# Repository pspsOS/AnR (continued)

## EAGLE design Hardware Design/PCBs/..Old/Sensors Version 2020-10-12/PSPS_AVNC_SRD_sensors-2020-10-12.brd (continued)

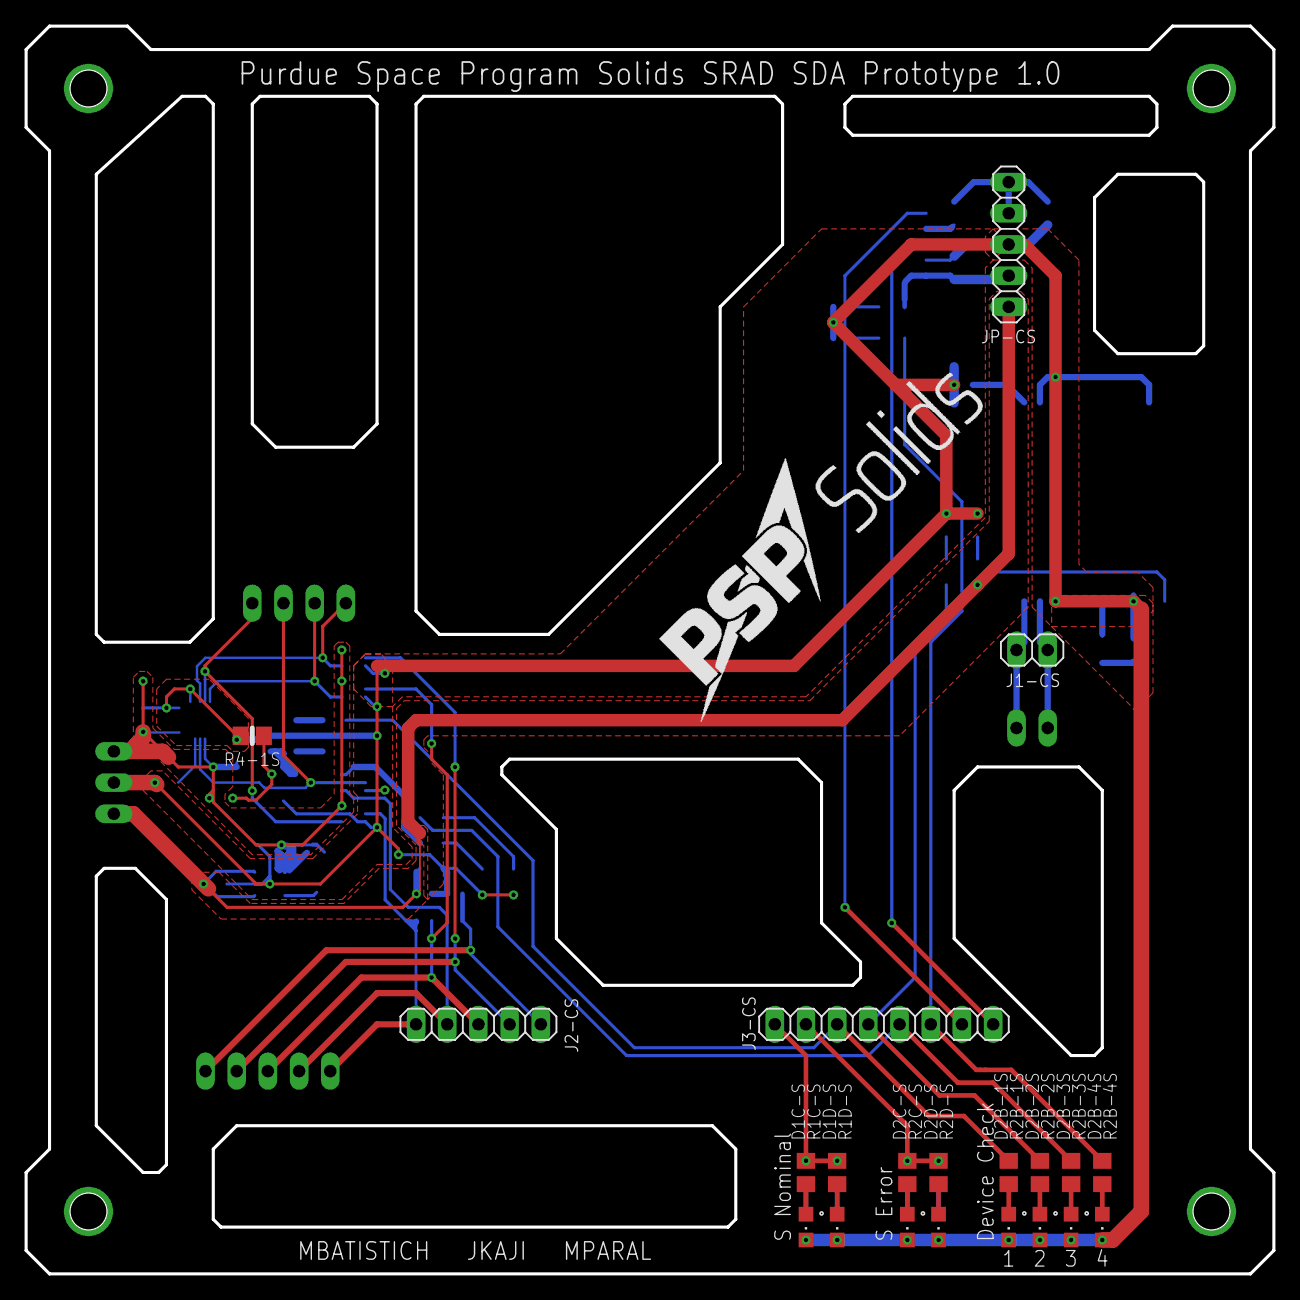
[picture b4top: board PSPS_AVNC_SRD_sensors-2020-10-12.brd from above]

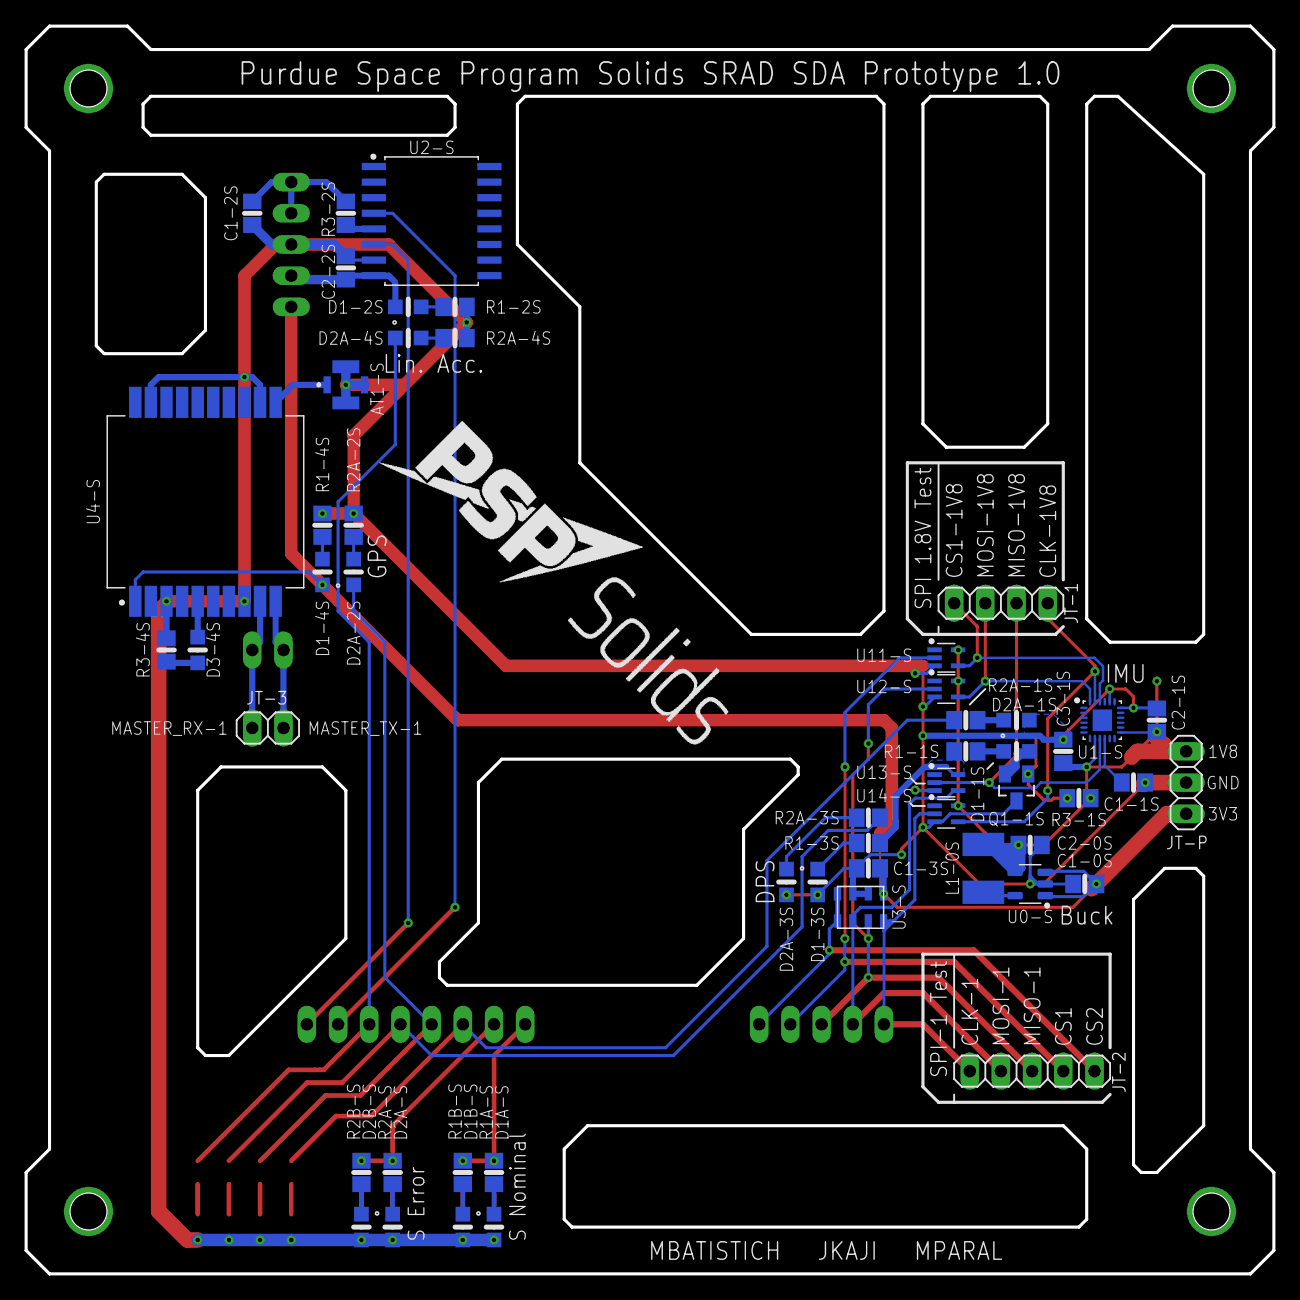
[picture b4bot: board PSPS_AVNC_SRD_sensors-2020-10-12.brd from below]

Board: 2 copper layers, 101.6 x 101.6 mm, 73 parts (52 on the bottom side), 52 nets.
